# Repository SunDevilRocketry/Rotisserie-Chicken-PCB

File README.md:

# Rotisserie-Chicken-PCB
PCB for controlling a motor that turns a rocket body tube while epoxy is drying

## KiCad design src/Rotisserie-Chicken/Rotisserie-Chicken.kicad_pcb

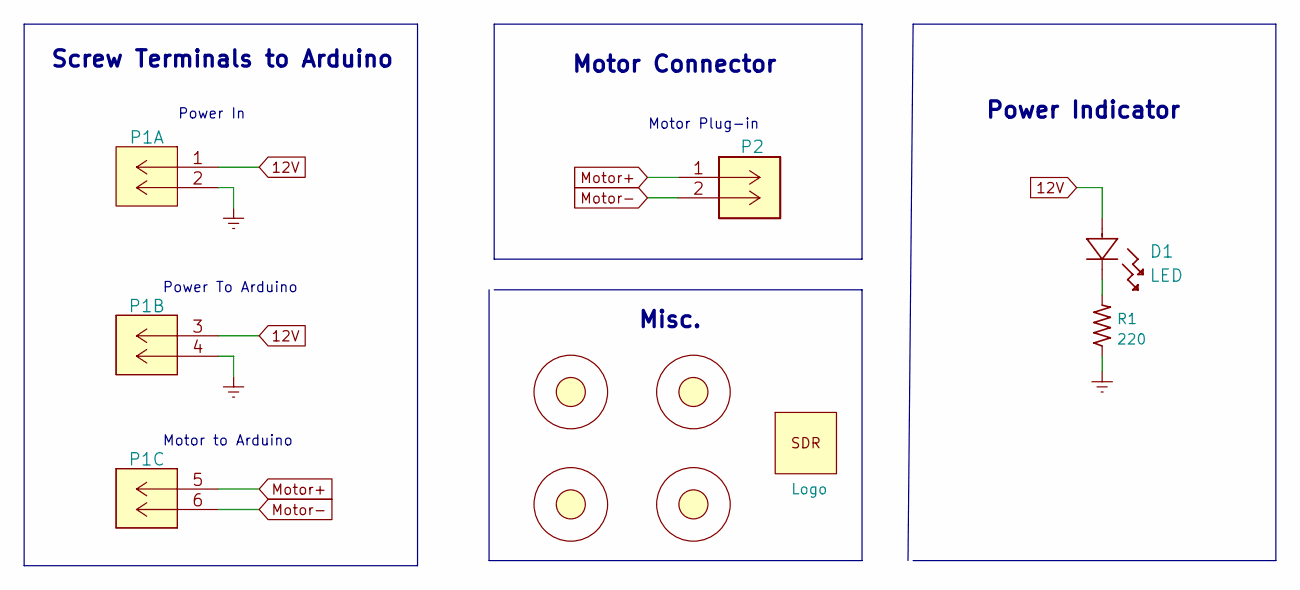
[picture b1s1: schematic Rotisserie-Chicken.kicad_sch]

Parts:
D1: LED
H1, H2, H3, H4: Mounting-Hole; MountingHole_4.3mm_M4_DIN965
LOGO1: Logo
P1: 282837-6
P2: 647676-2
R1: 220; RES_0603

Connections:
12V: D1.2, P1.1 (5), P1.3 (5)
Earth: P1.2 (6), P1.4 (6), R1.1
Motor+: P1.5, P2.1
Motor-: P1.6, P2.2
unnamed: D1.1, R1.2

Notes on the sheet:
Motor Plug-in
Power In
Power To Arduino
Power Indicator
Misc.
Screw Terminals to Arduino
Motor to Arduino
Motor Connector

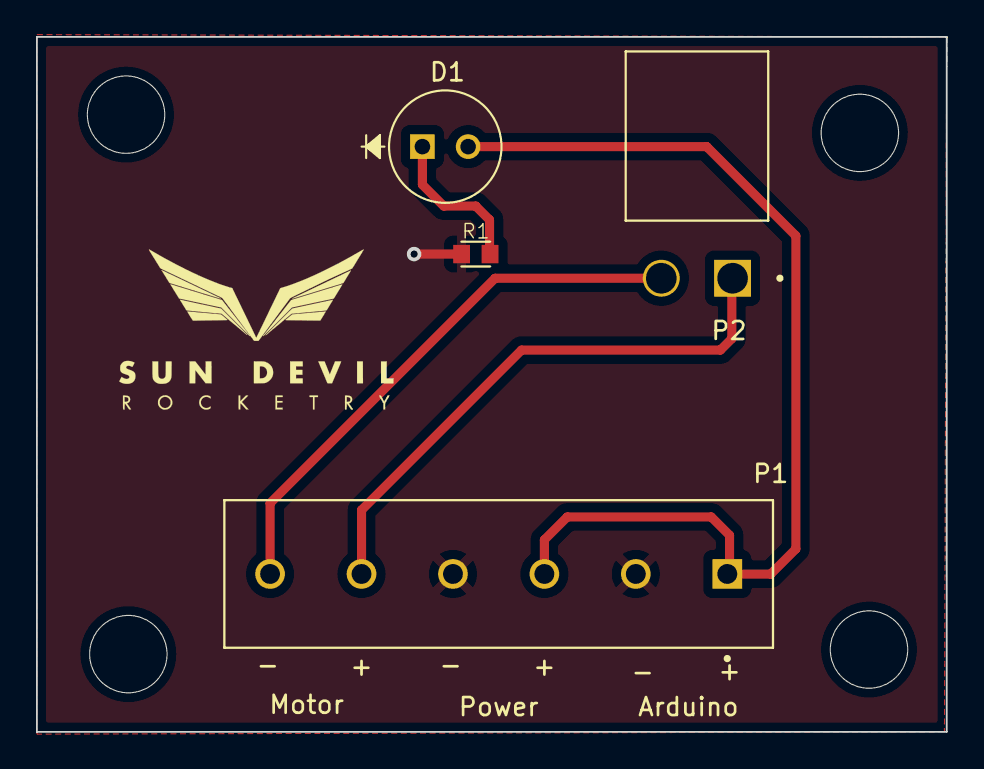
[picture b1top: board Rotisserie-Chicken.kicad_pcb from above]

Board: 2 copper layers, 50.5 x 38.6 mm, 9 parts (0 on the bottom side), 5 nets.

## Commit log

2022-12-06 copied over directory structure
2022-12-06 created lib files
2022-12-06 implemented schematic
2022-12-06 routed PCB
2022-12-06 added labels to screw terminals
2022-12-06 generated gerber files for production
